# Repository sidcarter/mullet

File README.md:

# mullet

A 67 key keyboard with USB Type-C and RGB underglow

Keyboard Maintainer: coseyfannitutti (https://github.com/coseyfannitutti)

Hardware Supported: mullet, atmega32u4  
Hardware Availability: https://github.com/coseyfannitutti

Make example for this keyboard (after setting up your build environment):

    make coseyfannitutti/mullet:default

See the [build environment setup](https://docs.qmk.fm/#/getting_started_build_tools) and the [make instructions](https://docs.qmk.fm/#/getting_started_make_guide) for more information. Brand new to QMK? Start with our [Complete Newbs Guide](https://docs.qmk.fm/#/newbs).

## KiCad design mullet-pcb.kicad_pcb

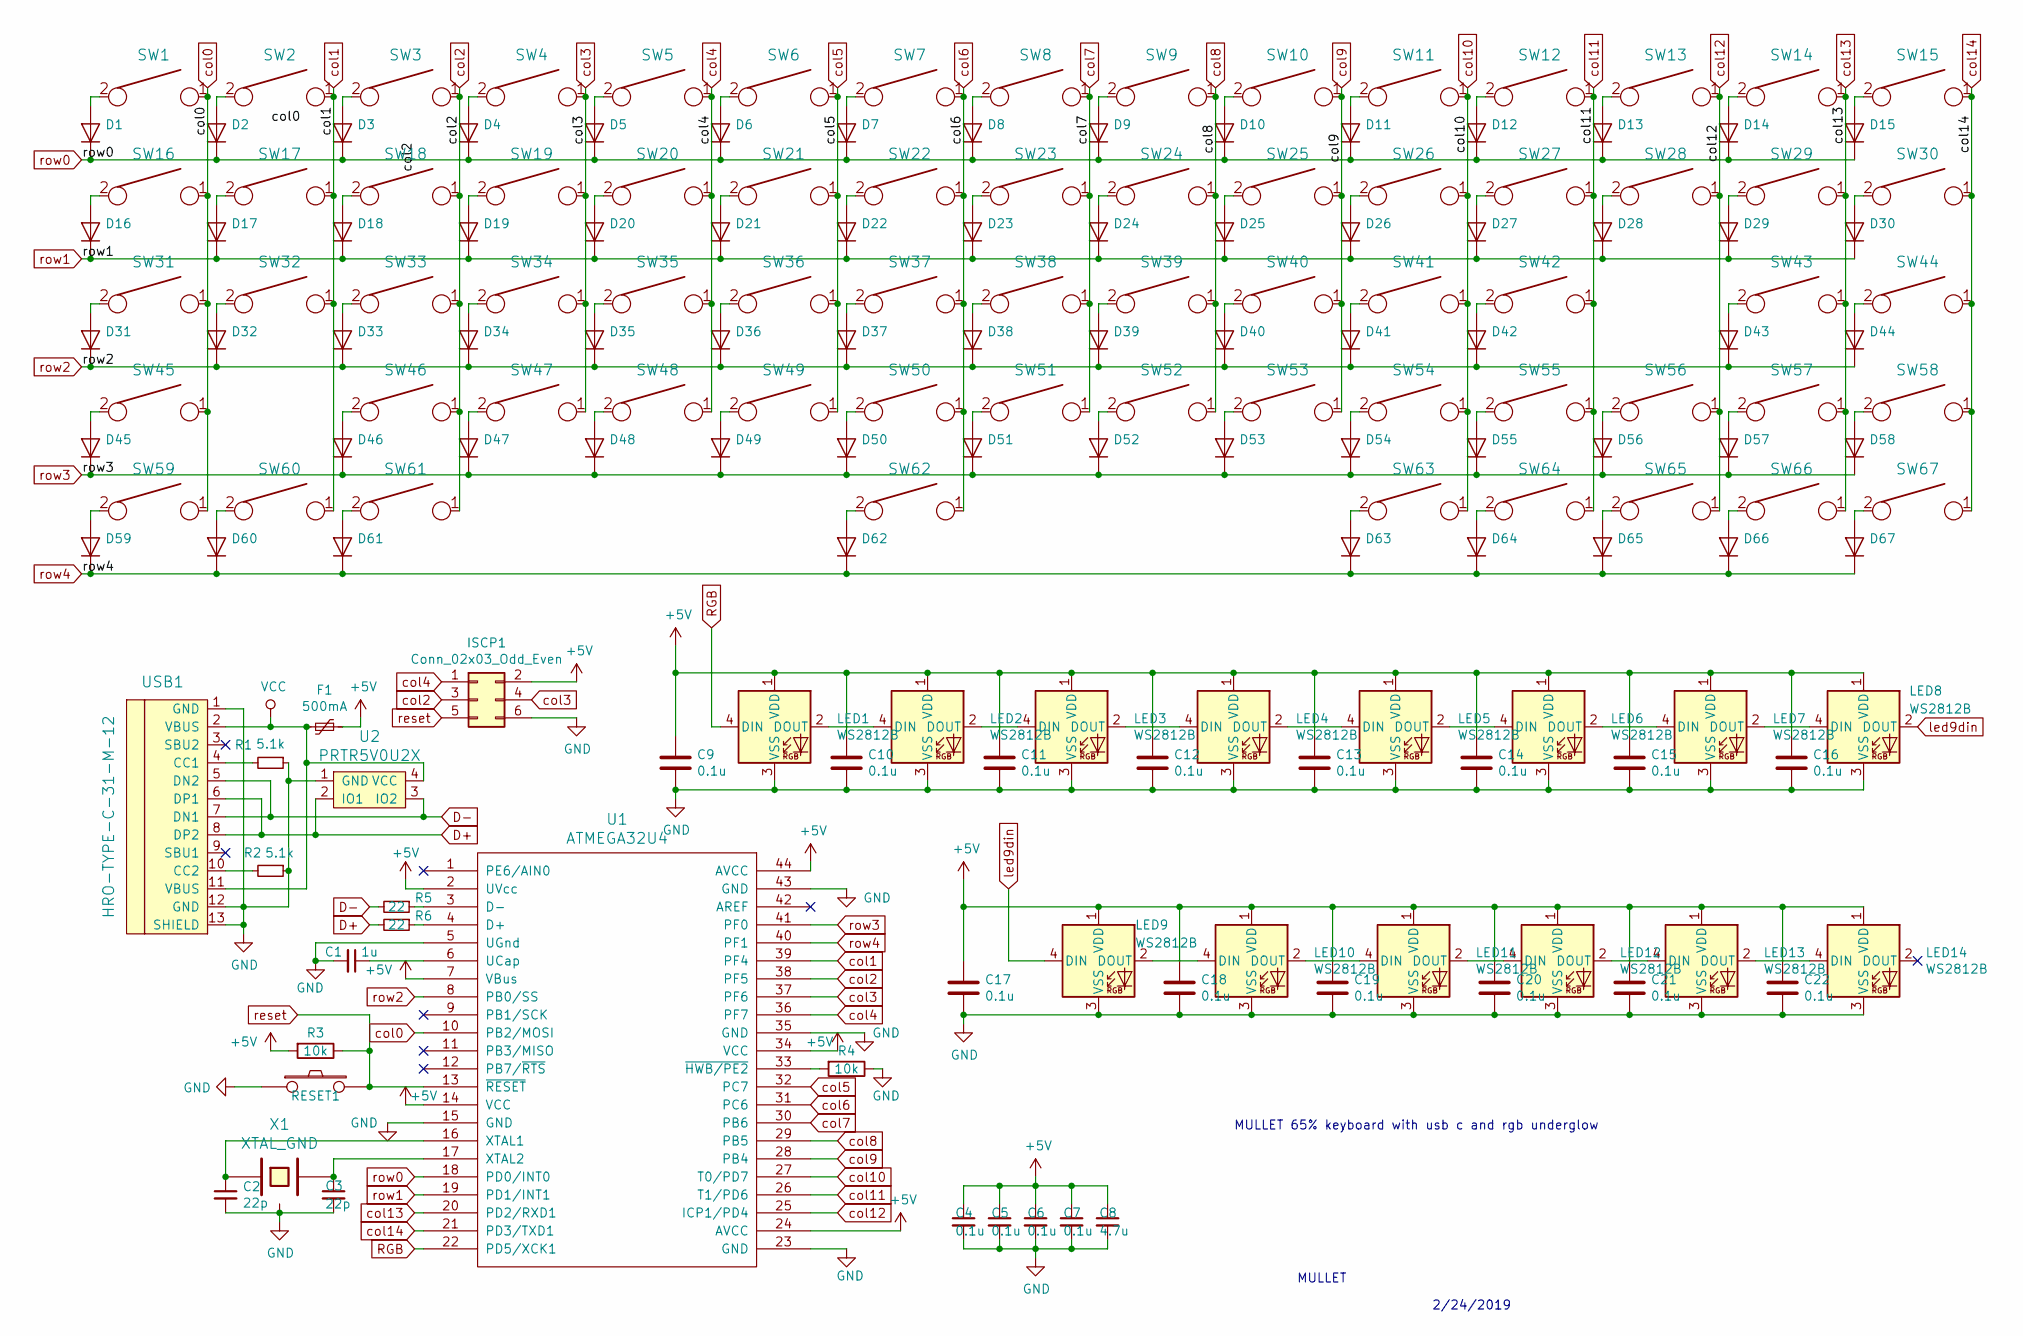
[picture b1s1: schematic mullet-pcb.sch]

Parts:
C1: 1u; C_0603_1608Metric
C2, C3: 22p; C_0603_1608Metric
C4, C5, C6, C7, C9, C10, C11, C12, C13, C14, C15, C16, C17, C18, C19, C20, C21, C22: 0.1u; C_0603_1608Metric
C8: 4.7u; C_0603_1608Metric
D1, D2, D3, D4, D5, D6, D7, D8, D9, D10, D11, D12, D13, D14, D15, D16, D17, D18, D19, D20, D21, D22, D23, D24, D25, D26, D27, D28, D29, D30, D31, D32, D33, D34, D35, D36, D37, D38, D39, D40, D41, D42, D43, D44, D45, D46, D47, D48, D49, D50, D51, D52, D53, D54, D55, D56, D57, D58, D59, D60, D61, D62, D63, D64, D65, D66, D67: D_SOD-123
F1: 500mA; R_0805_2012Metric
ISCP1: Conn_02x03_Odd_Even; AVR_ICSP_3x2
LED1, LED2, LED3, LED4, LED5, LED6, LED7, LED8, LED9, LED10, LED11, LED12, LED13, LED14: WS2812B; LED_WS2812B_PLCC4_5.0x5.0mm_P3.2mm
R1, R2: 5.1k; R_0603_1608Metric
R3, R4: 10k; R_0603_1608Metric
R5, R6: 22; R_0603_1608Metric
RESET1: SW_SPST_TL3342
SW1, SW2, SW3, SW4, SW5, SW6, SW7, SW8, SW9, SW10, SW11, SW12, SW13, SW15, SW17, SW18, SW19, SW20, SW21, SW22, SW23, SW24, SW25, SW26, SW27, SW28, SW30, SW32, SW33, SW34, SW35, SW36, SW37, SW38, SW39, SW40, SW41, SW42, SW44, SW46, SW47, SW48, SW49, SW50, SW51, SW52, SW53, SW54, SW55, SW57, SW58, SW62, SW65, SW66, SW67: KEYSW; SW_Cherry_MX1A_1.00u_PCB-NOSCREEN
SW14: KEYSW; SW_Cherry_MX1A_2.00u_PCBNOSCREEN
SW16, SW29: KEYSW; SW_Cherry_MX1A_1.50u_PCBNOSCREEN
SW31, SW56: KEYSW; SW_Cherry_MX1A_1.75u_PCBNOSCREEN
SW43, SW45: KEYSW; SW_Cherry_MX1A_2.25u_PCBNOSCREEN
SW59, SW60, SW61, SW63, SW64: KEYSW; SW_Cherry_MX1A_1.25u_PCBNOSCREEN
U1: ATMEGA32U4; QFN-44-1EP_7x7mm_Pitch0.5mm
U2: PRTR5V0U2X; SOT143B
USB1: HRO-TYPE-C-31-M-12; HRO-TYPE-C-31-M-12-HandSoldering
X1: XTAL_GND; FA-238

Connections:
+5V: C4.1, C5.1, C6.1, C7.1, C8.1, C9.1, C10.1, C11.1, C12.1, C13.1, C14.1, C15.1, C16.1, C17.1, C18.1, C19.1, C20.1, C21.1, C22.1, F1.1, ISCP1.2, LED1.1 (VDD), LED2.1 (VDD), LED3.1 (VDD), LED4.1 (VDD), LED5.1 (VDD), LED6.1 (VDD), LED7.1 (VDD), LED8.1 (VDD), LED9.1 (VDD), LED10.1 (VDD), LED11.1 (VDD), LED12.1 (VDD), LED13.1 (VDD), LED14.1 (VDD), R3.2, U1.2 (UVcc), U1.7 (VBus), U1.14 (VCC), U1.24 (AVCC), U1.34 (VCC), U1.44 (AVCC)
D+: R6.2, U2.2 (IO1), USB1.6 (DP1), USB1.8 (DP2)
D-: R5.2, U2.3 (IO2), USB1.5 (DN2), USB1.7 (DN1)
GND: C1.2, C2.2, C3.2, C4.2, C5.2, C6.2, C7.2, C8.2, C9.2, C10.2, C11.2, C12.2, C13.2, C14.2, C15.2, C16.2, C17.2, C18.2, C19.2, C20.2, C21.2, C22.2, ISCP1.6, LED1.3 (VSS), LED2.3 (VSS), LED3.3 (VSS), LED4.3 (VSS), LED5.3 (VSS), LED6.3 (VSS), LED7.3 (VSS), LED8.3 (VSS), LED9.3 (VSS), LED10.3 (VSS), LED11.3 (VSS), LED12.3 (VSS), LED13.3 (VSS), LED14.3 (VSS), R1.1, R2.1, R4.1, RESET1.1, U1.5 (UGnd), U1.15 (GND), U1.23 (GND), U1.35 (GND), U1.43 (GND), U2.1 (GND), USB1.1 (GND), USB1.12 (GND), USB1.13 (SHIELD), X1.3
unnamed: C1.1, U1.6 (UCap)
unnamed: C2.1, U1.16 (XTAL1), X1.1
unnamed: C3.1, U1.17 (XTAL2), X1.2
unnamed: D1.2 (A), SW1.2
unnamed: D2.2 (A), SW2.2
unnamed: D3.2 (A), SW3.2
unnamed: D4.2 (A), SW4.2
unnamed: D5.2 (A), SW5.2
unnamed: D6.2 (A), SW6.2
unnamed: D7.2 (A), SW7.2
unnamed: D8.2 (A), SW8.2
unnamed: D9.2 (A), SW9.2
unnamed: D10.2 (A), SW10.2
unnamed: D11.2 (A), SW11.2
unnamed: D12.2 (A), SW12.2
unnamed: D13.2 (A), SW13.2
unnamed: D14.2 (A), SW14.2
unnamed: D15.2 (A), SW15.2
unnamed: D16.2 (A), SW16.2
unnamed: D17.2 (A), SW17.2
unnamed: D18.2 (A), SW18.2
unnamed: D19.2 (A), SW19.2
unnamed: D20.2 (A), SW20.2
unnamed: D21.2 (A), SW21.2
unnamed: D22.2 (A), SW22.2
unnamed: D23.2 (A), SW23.2
unnamed: D24.2 (A), SW24.2
unnamed: D25.2 (A), SW25.2
unnamed: D26.2 (A), SW26.2
unnamed: D27.2 (A), SW27.2
unnamed: D28.2 (A), SW28.2
unnamed: D29.2 (A), SW29.2
unnamed: D30.2 (A), SW30.2
unnamed: D31.2 (A), SW31.2
unnamed: D32.2 (A), SW32.2
unnamed: D33.2 (A), SW33.2
unnamed: D34.2 (A), SW34.2
unnamed: D35.2 (A), SW35.2
unnamed: D36.2 (A), SW36.2
unnamed: D37.2 (A), SW37.2
unnamed: D38.2 (A), SW38.2
unnamed: D39.2 (A), SW39.2
unnamed: D40.2 (A), SW40.2
unnamed: D41.2 (A), SW41.2
unnamed: D42.2 (A), SW42.2
unnamed: D43.2 (A), SW43.2
unnamed: D44.2 (A), SW44.2
unnamed: D45.2 (A), SW45.2
unnamed: D46.2 (A), SW46.2
unnamed: D47.2 (A), SW47.2
unnamed: D48.2 (A), SW48.2
unnamed: D49.2 (A), SW49.2
unnamed: D50.2 (A), SW50.2
unnamed: D51.2 (A), SW51.2
unnamed: D52.2 (A), SW52.2
unnamed: D53.2 (A), SW53.2
unnamed: D54.2 (A), SW54.2
unnamed: D55.2 (A), SW55.2
unnamed: D56.2 (A), SW56.2
unnamed: D57.2 (A), SW57.2
unnamed: D58.2 (A), SW58.2
unnamed: D59.2 (A), SW59.2
unnamed: D60.2 (A), SW60.2
unnamed: D61.2 (A), SW61.2
unnamed: D62.2 (A), SW62.2
unnamed: D63.2 (A), SW63.2
unnamed: D64.2 (A), SW64.2
unnamed: D65.2 (A), SW65.2
unnamed: D66.2 (A), SW66.2
unnamed: D67.2 (A), SW67.2
unnamed: LED1.2 (DOUT), LED2.4 (DIN)
unnamed: LED2.2 (DOUT), LED3.4 (DIN)
unnamed: LED3.2 (DOUT), LED4.4 (DIN)
unnamed: LED4.2 (DOUT), LED5.4 (DIN)
unnamed: LED5.2 (DOUT), LED6.4 (DIN)
unnamed: LED6.2 (DOUT), LED7.4 (DIN)
unnamed: LED7.2 (DOUT), LED8.4 (DIN)
unnamed: LED10.2 (DOUT), LED11.4 (DIN)
unnamed: LED9.2 (DOUT), LED10.4 (DIN)
unnamed: LED11.2 (DOUT), LED12.4 (DIN)
unnamed: LED12.2 (DOUT), LED13.4 (DIN)
unnamed: LED13.2 (DOUT), LED14.4 (DIN)
unnamed: R1.2, USB1.4 (CC1)
unnamed: R2.2, USB1.10 (CC2)
unnamed: R4.2, U1.33 (~HWB/PE2)
unnamed: R5.1, U1.3 (D-)
unnamed: R6.1, U1.4 (D+)
RGB: LED1.4 (DIN), U1.22 (PD5/XCK1)
VCC: F1.2, U2.4 (VCC), USB1.2 (VBUS), USB1.11 (VBUS)
col0: SW1.1, SW16.1, SW31.1, SW45.1, SW59.1, U1.10 (PB2/MOSI)
col1: SW2.1, SW17.1, SW32.1, SW60.1, U1.39 (PF4)
col2: ISCP1.3, SW3.1, SW18.1, SW33.1, SW46.1, SW61.1, U1.38 (PF5)
col3: ISCP1.4, SW4.1, SW19.1, SW34.1, SW47.1, U1.37 (PF6)
col4: ISCP1.1, SW5.1, SW20.1, SW35.1, SW48.1, U1.36 (PF7)
col5: SW6.1, SW21.1, SW36.1, SW49.1, U1.32 (PC7)
col6: SW7.1, SW22.1, SW37.1, SW50.1, SW62.1, U1.31 (PC6)
col7: SW8.1, SW23.1, SW38.1, SW51.1, U1.30 (PB6)
col8: SW9.1, SW24.1, SW39.1, SW52.1, U1.29 (PB5)
col9: SW10.1, SW25.1, SW40.1, SW53.1, U1.28 (PB4)
col10: SW11.1, SW26.1, SW41.1, SW54.1, SW63.1, U1.27 (T0/PD7)
col11: SW12.1, SW27.1, SW42.1, SW55.1, SW64.1, U1.26 (T1/PD6)
col12: SW13.1, SW28.1, SW56.1, SW65.1, U1.25 (ICP1/PD4)
col13: SW14.1, SW29.1, SW43.1, SW57.1, SW66.1, U1.20 (PD2/RXD1)
col14: SW15.1, SW30.1, SW44.1, SW58.1, SW67.1, U1.21 (PD3/TXD1)
led9din: LED8.2 (DOUT), LED9.4 (DIN)
reset: ISCP1.5, R3.1, RESET1.2, U1.13 (~RESET)
row0: D1.1 (K), D2.1 (K), D3.1 (K), D4.1 (K), D5.1 (K), D6.1 (K), D7.1 (K), D8.1 (K), D9.1 (K), D10.1 (K), D11.1 (K), D12.1 (K), D13.1 (K), D14.1 (K), D15.1 (K), U1.18 (PD0/INT0)
row1: D16.1 (K), D17.1 (K), D18.1 (K), D19.1 (K), D20.1 (K), D21.1 (K), D22.1 (K), D23.1 (K), D24.1 (K), D25.1 (K), D26.1 (K), D27.1 (K), D28.1 (K), D29.1 (K), D30.1 (K), U1.19 (PD1/INT1)
row2: D31.1 (K), D32.1 (K), D33.1 (K), D34.1 (K), D35.1 (K), D36.1 (K), D37.1 (K), D38.1 (K), D39.1 (K), D40.1 (K), D41.1 (K), D42.1 (K), D43.1 (K), D44.1 (K), U1.8 (PB0/SS)
row3: D45.1 (K), D46.1 (K), D47.1 (K), D48.1 (K), D49.1 (K), D50.1 (K), D51.1 (K), D52.1 (K), D53.1 (K), D54.1 (K), D55.1 (K), D56.1 (K), D57.1 (K), D58.1 (K), U1.41 (PF0)
row4: D59.1 (K), D60.1 (K), D61.1 (K), D62.1 (K), D63.1 (K), D64.1 (K), D65.1 (K), D66.1 (K), D67.1 (K), U1.40 (PF1)

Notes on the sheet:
MULLET 65% keyboard with usb c and rgb underglow
2/24/2019
MULLET

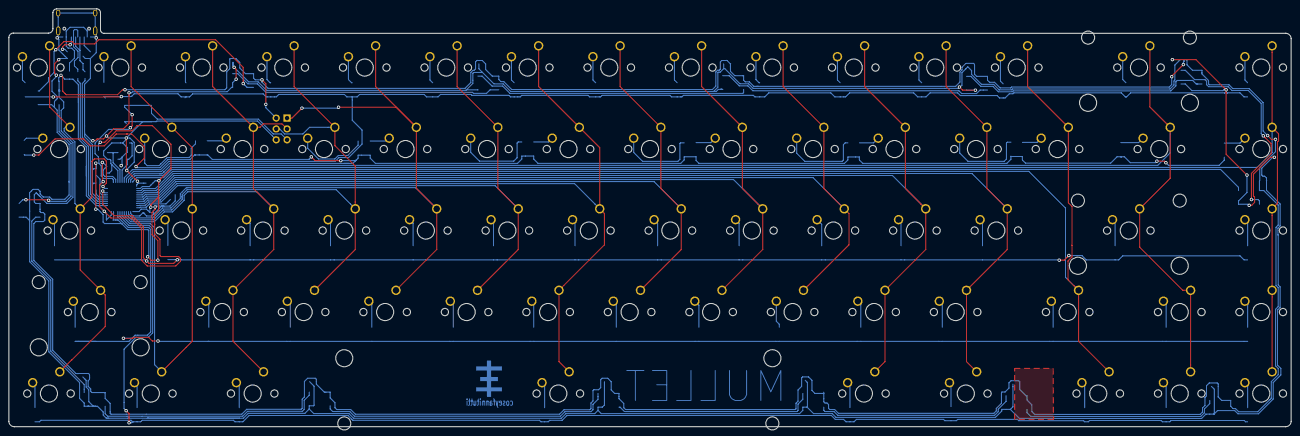
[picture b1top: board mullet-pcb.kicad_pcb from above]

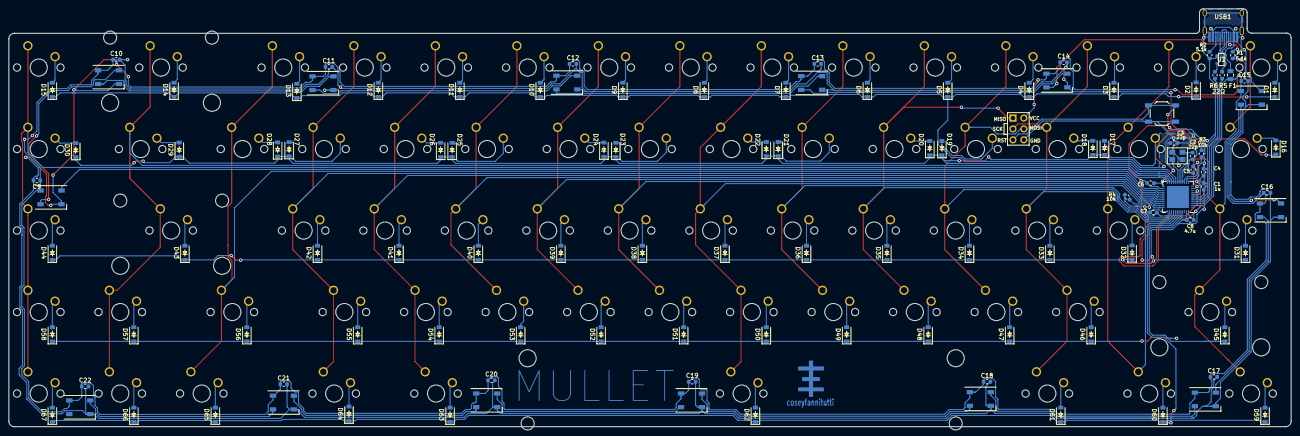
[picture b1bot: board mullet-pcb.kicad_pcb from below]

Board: 2 copper layers, 299.7 x 97.7 mm, 185 parts (116 on the bottom side), 115 nets.

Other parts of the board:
MULLETFRONT: LOGO; MULLET 9MM FMASK
ST62: KEYSW; Mx_Stab_625

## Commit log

2019-05-10 added plate drawing
2019-05-16 update ground fills for usb and xtal
2019-05-16 remove redundant qmk folder
2019-05-16 update ground fill for xtal
2019-05-17 Update gnd fills for xtal
2019-06-12 cleaned up traces
2019-06-12 update images
2019-06-13 cleaned up uneven tracks for aesthetic purposes
2019-06-20 added fillets to case middle layers
2019-06-26 clean up schematic
